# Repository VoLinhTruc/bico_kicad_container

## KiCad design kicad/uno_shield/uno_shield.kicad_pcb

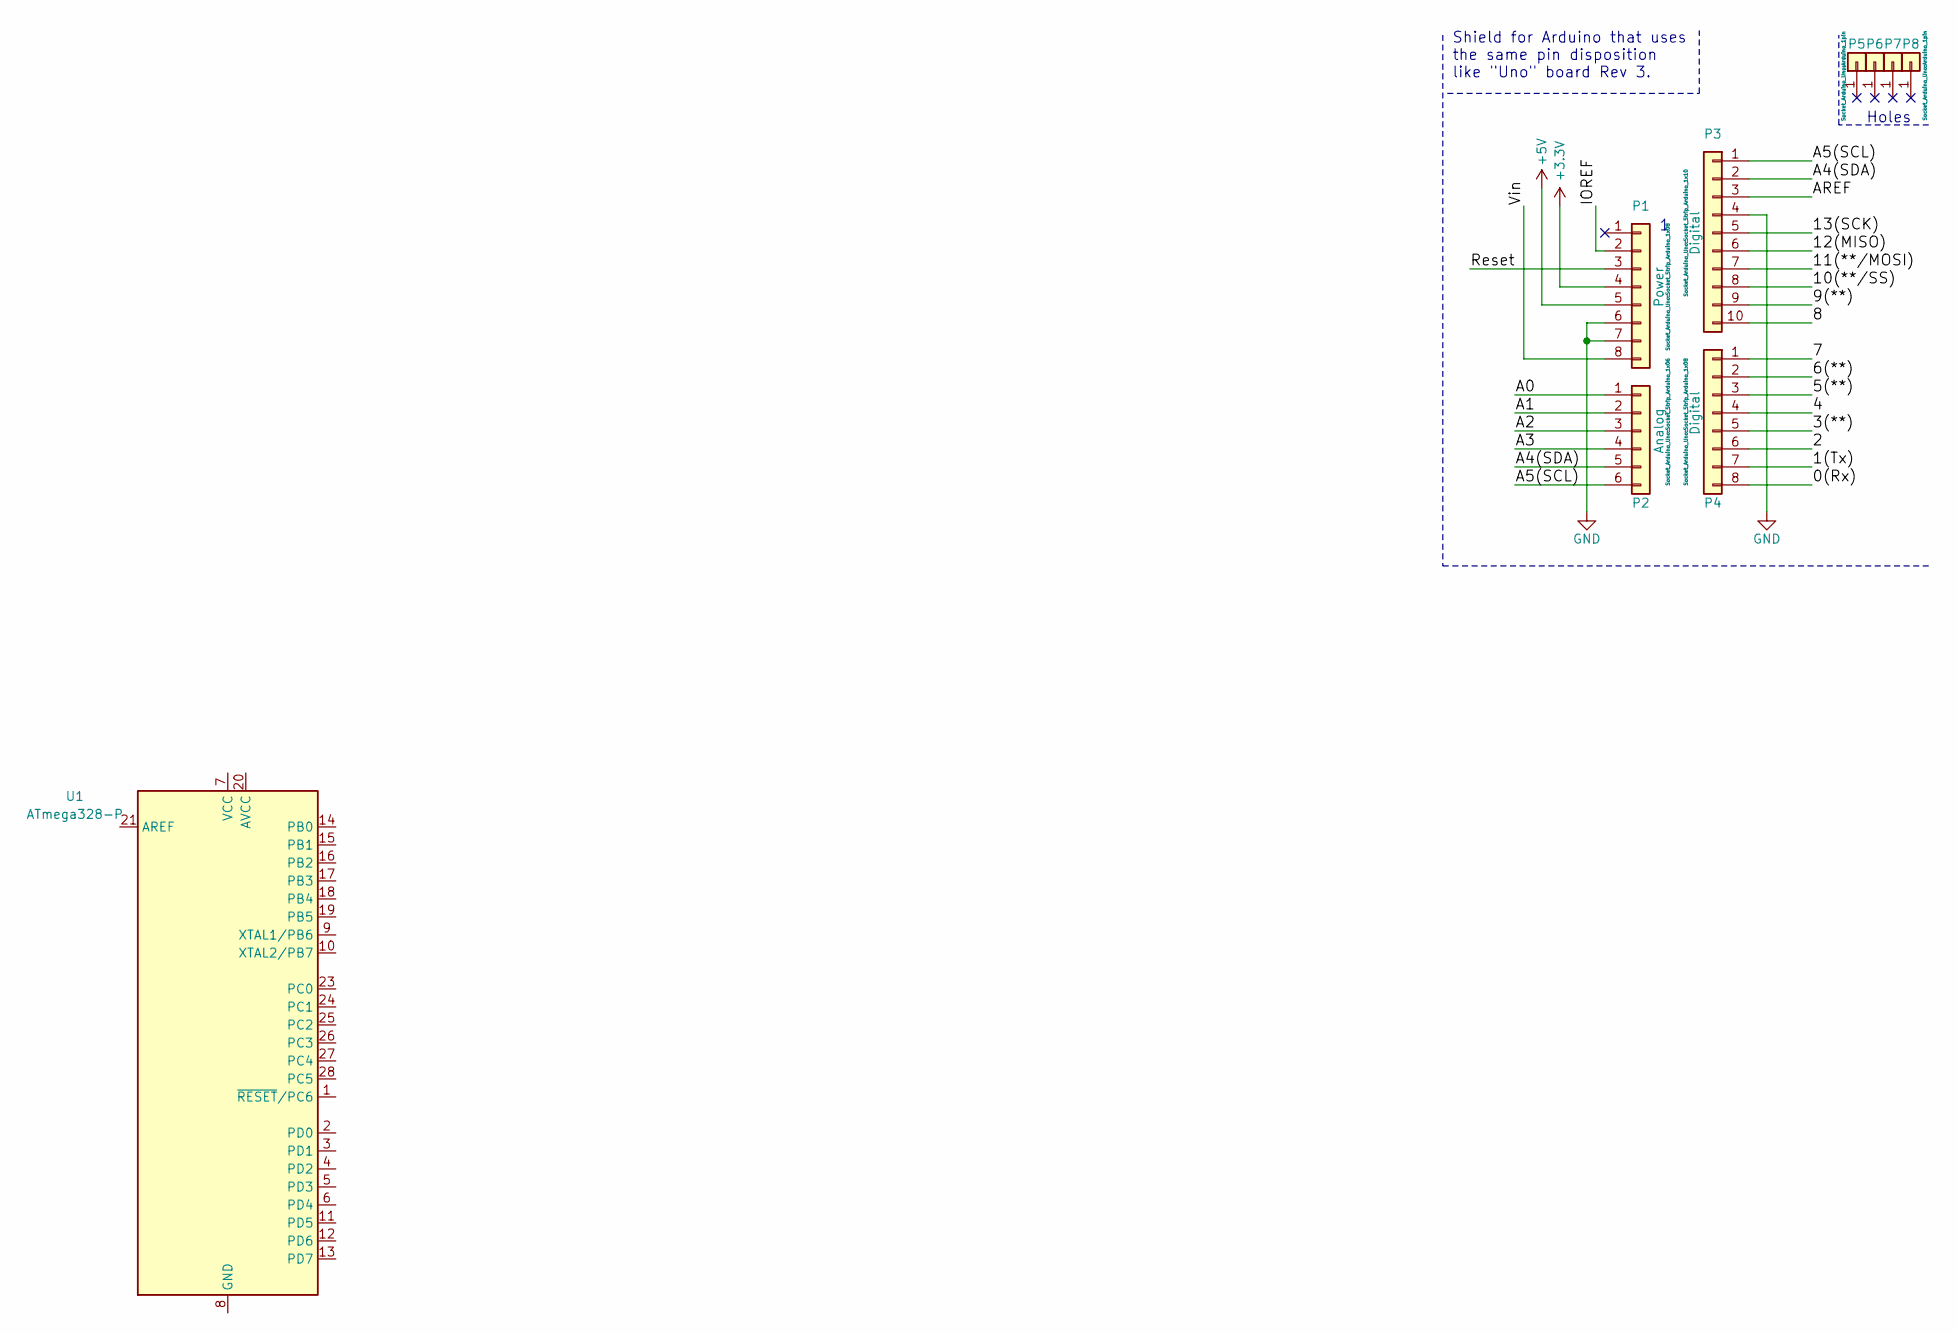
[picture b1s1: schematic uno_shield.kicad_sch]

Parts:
P1: Power; Socket_Strip_Arduino_1x08
P2: Analog; Socket_Strip_Arduino_1x06
P3: Digital; Socket_Strip_Arduino_1x10
P4: Digital; Socket_Strip_Arduino_1x08
P5, P6, P7, P8: CONN_01X01; Arduino_1pin
U1: ATmega328-P; DIP-28_W7.62mm

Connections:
+3V3: P1.4
+5V: P1.5
/0(Rx): P4.8
/1(Tx): P4.7
/2: P4.6
/3(**): P4.5
/4: P4.4
/5(**): P4.3
/6(**): P4.2
/7: P4.1
/8: P3.10
/9(**): P3.9
/10(**/SS): P3.8
/11(**/MOSI): P3.7
/12(MISO): P3.6
/13(SCK): P3.5
/A0: P2.1
/A1: P2.2
/A2: P2.3
/A3: P2.4
/A4(SDA): P2.5, P3.2
/A5(SCL): P2.6, P3.1
/AREF: P3.3
/IOREF: P1.2
/Reset: P1.3
/Vin: P1.8
GND: P1.6, P1.7, P3.4
unnamed: U1.8 (GND), U1.22 (GND)

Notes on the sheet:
Holes
Shield for Arduino that uses the same pin disposition like "Uno" board Rev 3.

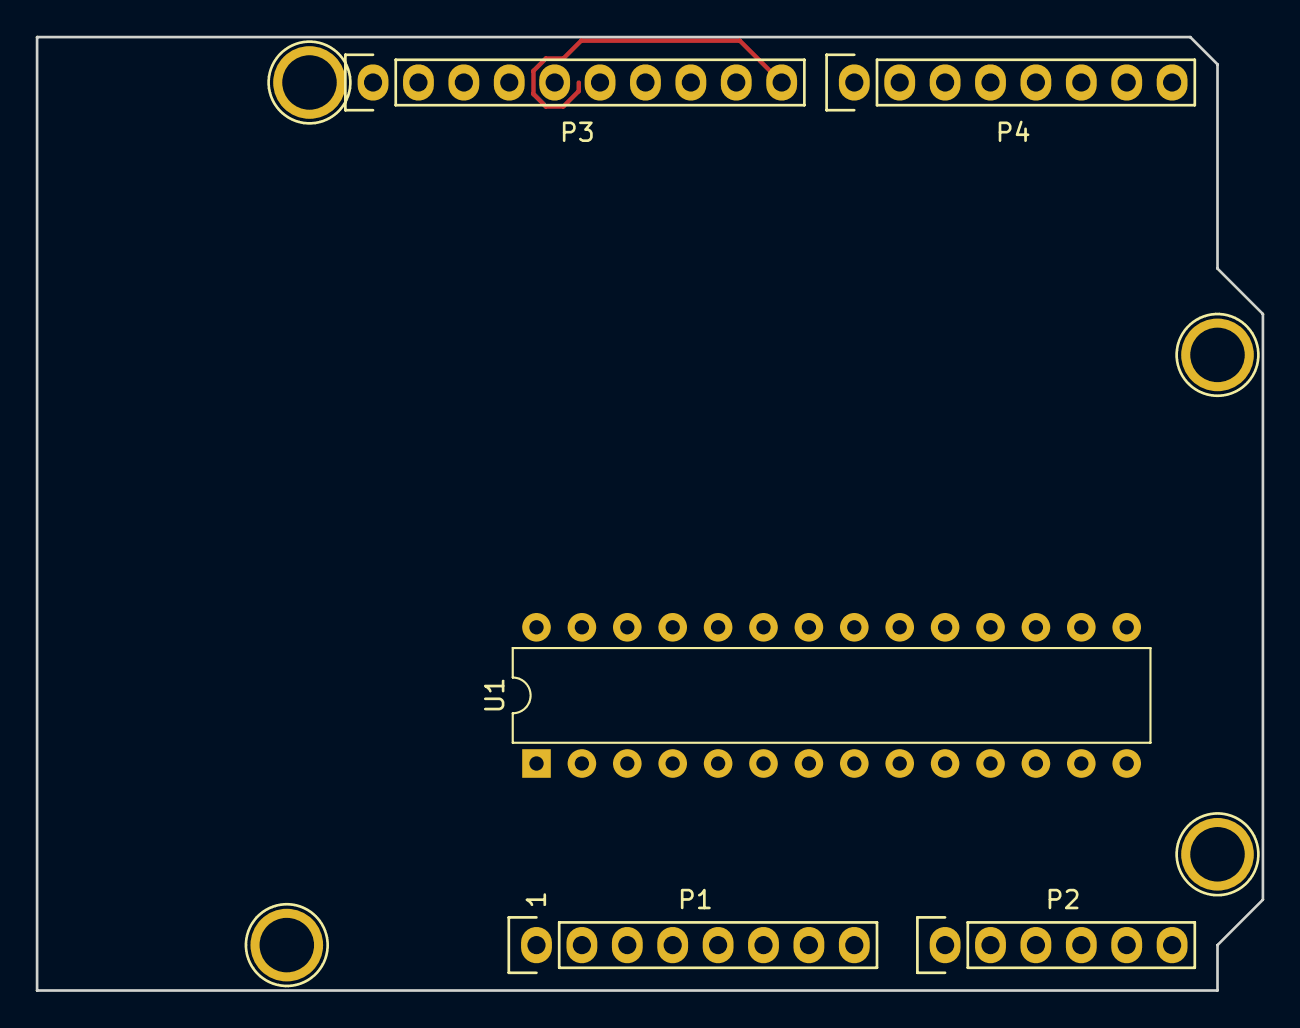
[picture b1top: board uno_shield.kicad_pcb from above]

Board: 2 copper layers, 68.6 x 53.3 mm, 9 parts (0 on the bottom side), 4 nets.

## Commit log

2025-12-03 add kicad Uno shield project
2025-12-03 update to enable dark theme by default
2025-12-03 complete the hgt_lab_wiring, output in hgt_lab/hgt_lab/hgt_lab.svg
2025-12-03 comment out the dark theme setup, get back to KiCAD default theme. Reason: easier to color the schematic, in dark theme even the wrire colore set to green or red, what I see is dark red
2025-12-04 add annotation for hgt_lab schematic
2025-12-04 update schematic and generate the pdf file
2025-12-06 update docker file to clean cache -> reduce image size
2025-12-22 fix docker image build error
2025-12-22 update hgt_lab
